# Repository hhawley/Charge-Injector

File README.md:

# Charge Injector

The amplifier used in my setup could not be calibrated using a sine wave as the gain parameter was a wide-band gain (from few kHz to 200 MHz). Ideally, this gain can be calculated when the amplifier is injected with a pulse with a known total integrated charge. The total charge can be estimated with the next equation

$Q = \Delta V C$

This charge injector (or whatever is the official technical name, I could never find it!) was built with the most accurate capacitor I could buy which is a  9.1 pF, $C$, 0.5% NP0 resistor. This circuit needs a high precision (in voltage) square square to work. I made mine with a 10V precision voltage reference, a 10:1 voltage divider (for a 1Vpp square wave), and a signal relay.

The main contributor to the error budget comes from $C$ and everything else contributed almost nothing.

However, the final design was a "failure". Problems such as not enough filtering of the power rails (which was solved with enough hand-soldered capacitors: see the picture!) and the noise mostly dominated at low frequency  (1-10 kHz) made this design not really suitable for the application.

It was a good project built and tested within 2-3 weeks.

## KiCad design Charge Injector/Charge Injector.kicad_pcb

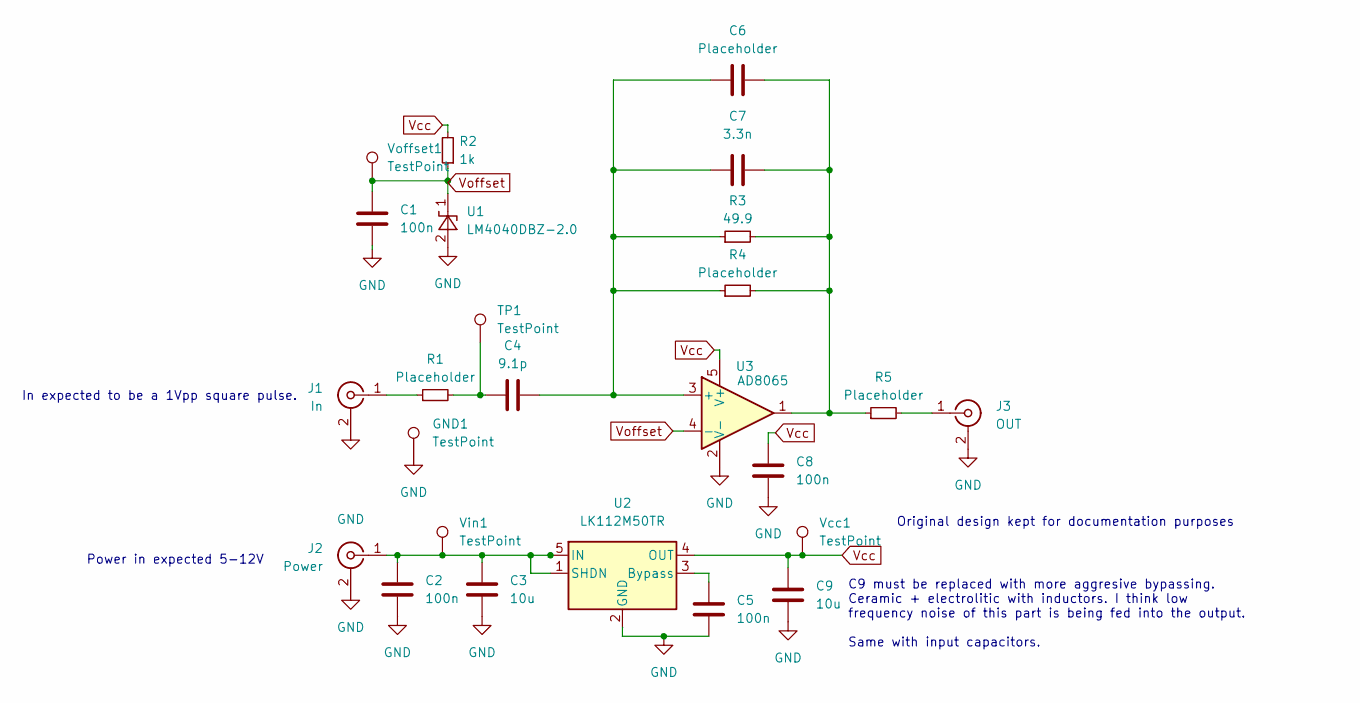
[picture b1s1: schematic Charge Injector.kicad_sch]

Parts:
C1, C2, C5, C8: 100n; C_0603_1608Metric_Pad1.08x0.95mm_HandSolder
C3, C9: 10u; C_1206_3216Metric_Pad1.33x1.80mm_HandSolder
C4: 9.1p; C_0402_1005Metric_Pad0.74x0.62mm_HandSolder
C6: Placeholder; C_0603_1608Metric_Pad1.08x0.95mm_HandSolder
C7: 3.3n; C_0603_1608Metric_Pad1.08x0.95mm_HandSolder
GND1: TestPoint; TestPoint_Pad_D1.5mm
J1: In; SMA_Samtec_SMA-J-P-X-ST-EM1_EdgeMount
J2: Power; SMA_Samtec_SMA-J-P-X-ST-EM1_EdgeMount
J3: OUT; SMA_Samtec_SMA-J-P-X-ST-EM1_EdgeMount
R1, R4, R5: Placeholder; R_1206_3216Metric_Pad1.30x1.75mm_HandSolder
R2: 1k; R_0603_1608Metric_Pad0.98x0.95mm_HandSolder
R3: 49.9; C_0805_2012Metric_Pad1.18x1.45mm_HandSolder
TP1: TestPoint; TestPoint_Pad_D1.5mm
U1: LM4040DBZ-2.0; SOT-23
U2: LK112M50TR; SOT-23-5
U3: AD8065; SOT-23-5
Vcc1: TestPoint; TestPoint_Pad_D1.5mm
Vin1: TestPoint; TestPoint_Pad_D1.5mm
Voffset1: TestPoint; TestPoint_Pad_D1.5mm

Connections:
GND: C1.2, C2.2, C3.2, C5.2, C8.2, C9.2, GND1.1, J1.2 (Ext), J2.2 (Ext), J3.2 (Ext), U1.2 (A), U2.2 (GND), U3.2 (V-)
unnamed: C4.1, R1.2, TP1.1
unnamed: C6.2, C7.1, R3.2, R4.2, R5.1, U3.1
unnamed: J1.1 (In), R1.1
unnamed: C2.1, C3.1, J2.1 (In), U2.1 (SHDN), U2.5 (IN), Vin1.1
unnamed: J3.1 (In), R5.2
unnamed: C5.1, U2.3 (Bypass)
unnamed: C4.2, C6.1, C7.2, R3.1, R4.1, U3.3 (+)
Vcc: C8.1, C9.1, R2.2, U2.4 (OUT), U3.5 (V+), Vcc1.1
Voffset: C1.1, R2.1, U1.1 (K), U3.4 (-), Voffset1.1

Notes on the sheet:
C9 must be replaced with more aggresive bypassing. Ceramic + electrolitic with inductors. I think low frequency noise of this part is being fed into the output. Same with input capacitors.
Original design kept for documentation purposes
Power in expected 5-12V
In expected to be a 1Vpp square pulse.

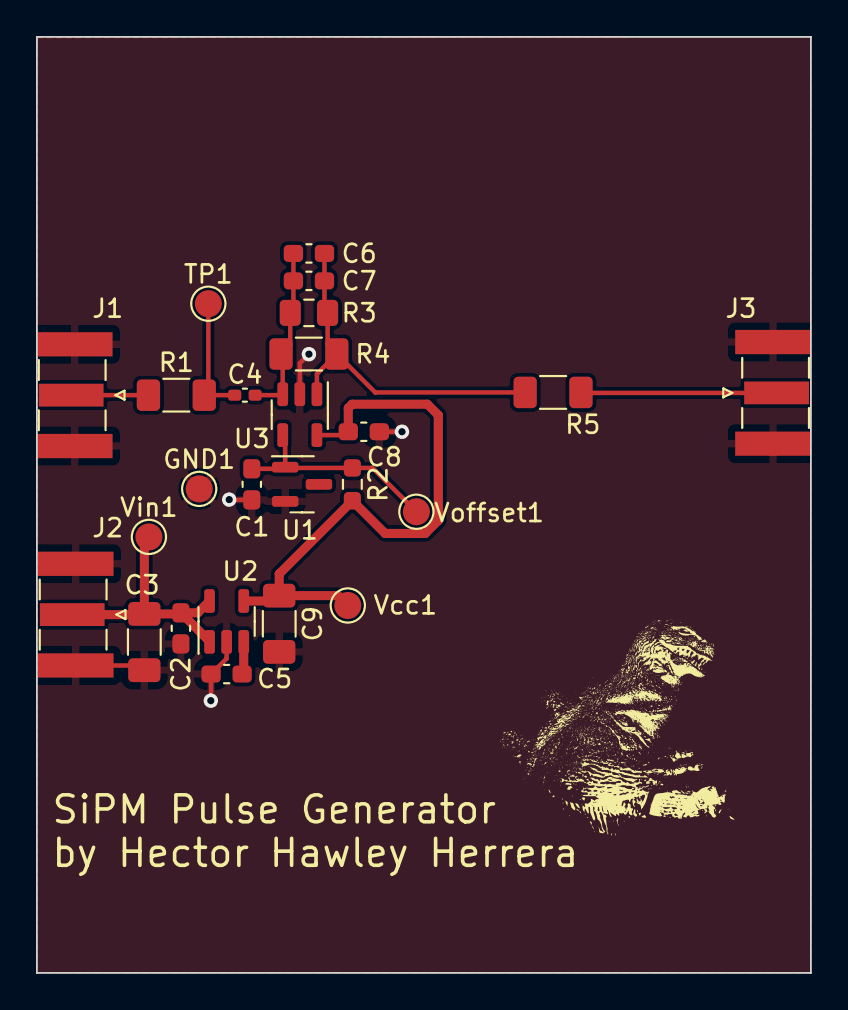
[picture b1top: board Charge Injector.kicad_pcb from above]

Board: 2 copper layers, 43.0 x 52.0 mm, 25 parts (0 on the bottom side), 10 nets.

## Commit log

2023-11-22 Uploaded the final charge injector used in the lab
